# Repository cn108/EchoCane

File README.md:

# EchoCane — Arduino Nano Smart-Cane Prototype

**A safety-first embedded systems project: portable C++ policy core, Arduino Nano firmware, HC-SR04 sensing, PWM haptic drive, KiCad hardware and a documented verification trail.**

EchoCane is an experimental supplementary mobility aid that measures the distance
to the nearest surface with an HC-SR04 ultrasonic sensor and gives graded tactile
and audible warnings. This repository reconstructs the concept as a complete,
testable embedded-engineering portfolio project: portable C++ policy code,
Arduino Nano firmware, Wokwi simulation assets, native unit tests, a KiCad
carrier board, manufacturing outputs and engineering documentation.

> **Project intent:** this is an engineering case study, not a medical device or
a validated navigation product. The interesting part is the discipline around
it: bounded sensing, explicit fault behaviour, host-testable policy code,
power/thermal checks, editable PCB sources and an honest limitations register.

> **Safety notice**
> EchoCane is an experimental supplementary aid. It is **not** a replacement for
> a conventional mobility cane and has **not** been validated with users or on
> physical hardware. The distance thresholds in this repository are demonstration
> parameters, not safety limits. Do not use this design as a sole mobility aid.

> **Evidence notice**
> No physical Arduino, sensor, motor or PCB was available. Firmware compilation,
> host unit tests, schematic/PCB checks and an ngspice driver simulation were
> executed. Wokwi assets were validated structurally, but the Wokwi scenarios
> were **not executed** here because the Wokwi CLI and CI token were unavailable.
> Simulation is not physical validation.

## Contents

- [The problem](#the-problem)
- [What this project demonstrates](#what-this-project-demonstrates)
- [Demonstrated behaviour](#demonstrated-behaviour)
- [Status at a glance](#status-at-a-glance)
- [Visual gallery](#visual-gallery)
- [Features](#features)
- [Technology stack](#technology-stack)
- [Architecture](#architecture)
- [Repository layout](#repository-layout)
- [Quick start](#quick-start)
- [PCB](#pcb)
- [Engineering decisions and trade-offs](#engineering-decisions-and-trade-offs)
- [Pin map](#pin-map)
- [Audit corrections](#audit-corrections)
- [Engineering limitations](#engineering-limitations)
- [Documentation](#documentation)
- [License](#license)

## The problem

A white cane is effective because it gives direct, continuous mechanical feedback
about the ground and nearby objects. An electronic aid can complement it by
warning about obstacles before contact, but it introduces new failure modes:
sensor dropouts, blind angles, false confidence and output masking. EchoCane is
therefore designed around an explicit safety rule:

**A failed or unavailable sensor must never be reported as an obstacle-free path.**

The project explores that rule through a small, understandable system rather than
claiming to solve navigation for visually impaired users.

## What this project demonstrates

- **Safety-first firmware policy.** Invalid sensor readings never map to a
  clear-path result; the system moves through `CAUTION`/`FAULT`, requires
  consecutive confirmations, and only recovers after consecutive valid reads.
- **A testable embedded architecture.** Classification, hysteresis, debounce,
  scheduling and mode policy live in a portable C++ library with no Arduino
  dependency; hardware-specific `pulseIn`, `analogWrite`, `tone` and `millis`
  adapters stay at the edge.
- **Resource-aware AVR work.** The Nano build is constrained and measured:
  **10,766 / 30,720 bytes flash (35.0%)** and **777 / 2,048 bytes RAM (37.9%)**.
- **Real hardware engineering.** A complete KiCad 10 schematic and 2-layer PCB,
  editable sources, Gerbers, Excellon drill, drill map, STEP, schematic/PCB
  previews and an independent ERC/DRC/parity trail.
- **Analog and power reasoning.** The motor driver was sized around the loaded
  ATmega328P GPIO, R2 loading and a forced-beta target; the 1N4007 was checked
  against the actual 976.56 Hz PWM period and the design-current margins.
- **Reproducible evidence.** Deterministic schematic/PCB generators,
  cross-artifact validators, native unit tests and simulator assets are checked
  into the repository instead of being described only in prose.
- **Engineering honesty.** The audit findings, unresolved physical-validation
  gaps and design limitations are published alongside the passing checks.

### How to review this repository

| If you have… | Start here |
|---|---|
| 2 minutes | This README, then the [schematic](hardware/schematic/EchoCane-schematic.pdf) |
| 10 minutes | [Architecture](docs/architecture.md) and [circuit explanation](docs/circuit-explanation.md) |
| 30 minutes | [Independent audit](docs/audit-report.md), [requirements](docs/requirements.md) and [testing strategy](docs/testing-strategy.md) |
| A hardware/embedded interview | [Engineering decisions](#engineering-decisions-and-trade-offs), [pin map](#pin-map), [limitations](#engineering-limitations) |

## Demonstrated behaviour

| Measured distance | Alert level | Haptic pattern | Buzzer (Assist/Diagnostic) | LED |
|---|---|---|---|---|
| > 150 cm | `CLEAR` | off | off | short heartbeat |
| 80–150 cm inclusive | `CAUTION` | 40 %, 180 ms on / 320 ms off | 1800 Hz, 60 ms / 1140 ms | 120 ms blink |
| < 80 cm | `DANGER` | 100 %, 400 ms on / 120 ms off | 2400 Hz, 90 ms / 210 ms | solid |
| invalid / timeout | `CAUTION` first, then `FAULT` | fault pattern | 1000 Hz fault pattern | fast fault blink |

Hysteresis is asymmetric: a warning engages at the threshold but releases only
after the distance improves by 10 cm. This prevents chatter around 80 cm and
150 cm. The exact policy is in
[`ObstacleDetector.cpp`](firmware/lib/echocane_core/src/ObstacleDetector.cpp)
and is covered by unit tests.

A confirmed sensor fault requires **3 consecutive invalid acquisitions**. Recovery
requires **3 consecutive valid acquisitions**, and the system remains at least at
`CAUTION` while degraded or recovering. A failed acquisition holds the last
warning rather than clearing it.

## Status at a glance

| Check | Result | Evidence |
|---|---|---|
| Arduino Nano firmware build | **PASS** — 10,766 / 30,720 bytes flash (35.0 %), 777 / 2,048 bytes RAM (37.9 %) | PlatformIO `nanoatmega328` |
| Host unit tests | **PASS** — 25 / 25 | `pio test -e native` |
| Wokwi structural validation | **PASS** — 6 diagrams with explicit pin/stimulus mappings, 0 warnings | `python tests/validate_simulation.py` |
| Wokwi scenario execution | **NOT VERIFIED (NOT RUN)** — CLI/token unavailable | no serial logs claimed |
| Schematic ERC | **PASS** — 0 errors, 0 warnings | `hardware/verification/schematic-erc.rpt` |
| PCB DRC | **PASS** — 0 DRC violations, 0 unconnected pads, 0 schematic-parity issues | `hardware/verification/pcb-drc.rpt` |
| Cross-artifact consistency | **PASS** — 12 nets, 19 components, 15 BOM rows, 8 Wokwi links agree | `python tests/validate_hardware.py` |
| Driver design margins | **PASS** — 270 Ω, 4.2 V loaded GPIO, 11.0 mA base, forced beta 9.10 | `simulation/simulide/driver-analysis.json` |
| ngspice driver simulation | **EXECUTED** — 12.04 mA base, 104.37 mA motor, 0.0945 V Vce, 5.63 V flyback clamp | `simulation/simulide/ngspice-results.txt` |
| Independent engineering audit | **PASS** for every available check; physical/external checks remain open | [`docs/audit-report.md`](docs/audit-report.md) |
| Remote GitHub Actions execution | **PASS** — firmware/tests and KiCad ERC/DRC jobs completed successfully on GitHub | [EchoCane CI run 43788851832](https://github.com/cn108/EchoCane/actions/runs/43788851832) |
| Physical hardware / user validation | **NOT VERIFIED (not performed)** | no hardware available |

## Visual gallery

<p align="center">
  <em>A4 schematic with visible functional-block wiring; 3D top render of the 100 × 85 mm carrier PCB.</em>
</p>

Additional views: [schematic PDF](hardware/schematic/EchoCane-schematic.pdf),
[PCB PDF](hardware/pcb/EchoCane-pcb.pdf),
[3D bottom](images/EchoCane-3d-bottom.png),
[driver waveform](images/driver-waveform.svg).

## Features

- Cooperative application loop with 60 ms sensor scans, 5 ms button polling and
  scheduled haptic/audio/LED patterns. The HC-SR04 acquisition is bounded but
  blocking for up to 25 ms; it is not a hard-real-time loop.
- Five-sample median filter, asymmetric hysteresis, invalid-reading handling,
  timeout detection, fault confirmation and recovery.
- Three operating modes: **Assist** (haptic + audio), **Quiet** (haptic only) and
  **Diagnostic** (full warnings plus faster telemetry).
- Portable `echocane_core` library with no Arduino dependencies; host-testable
  policy and hardware adapters behind small interfaces.
- Serial diagnostics with a stable machine-readable `EC|...` telemetry record.
- Complete KiCad 10 schematic, 2-layer carrier PCB, 3D render, Gerbers and drill
  files.
- Reproducible hardware generators for the schematic, PCB and BOM.

## Technology stack

| Layer | Tool / part |
|---|---|
| Microcontroller | Arduino Nano, ATmega328P, classic 5 V, 16 MHz |
| Firmware | C++17, Arduino framework, PlatformIO |
| Host tests | PlatformIO native environment + Unity |
| Simulation | Wokwi (Arduino Nano, HC-SR04, LEDs, buzzer, button) |
| Supplementary circuit analysis | ngspice transient model; SimulIDE build guide |
| PCB | KiCad 10.0.8, `kicad-cli`, Docker |
| CI | GitHub Actions (build, tests, validators, KiCad checks, optional Wokwi) |

## Architecture

```mermaid
flowchart LR
  HC["HC-SR04<br/>D9 TRIG / D10 ECHO"] --> SM[SensorManager<br/>Arduino adapter]
  BTN["Mode button<br/>D2"] --> DB[ButtonDebouncer<br/>portable]
  SM -->|DistanceReading| EC[EchoCaneController<br/>portable policy]
  DB -->|validated press| EC
  EC --> HP[HapticController<br/>D6 PWM]
  EC --> AU[AudioController<br/>D8 tone]
  EC --> LD[LedIndicator<br/>D7]
  EC --> SR[SerialReporter<br/>115200 baud]
```

The core owns classification, hysteresis, fault/recovery, mode selection and
alert-pattern selection. The Arduino adapters own pins, `pulseIn`, `analogWrite`,
`tone` and `millis`. `EchoCaneController` can therefore be compiled and tested on
a host without an Arduino.

## Repository layout

```text
EchoCane/
├── firmware/
│   ├── include/                 # Arduino-facing adapters and pin map
│   ├── src/                     # SensorManager, outputs, main.cpp
│   ├── lib/echocane_core/       # portable policy library
│   └── test/test_core/          # 25 Unity tests, native environment
├── hardware/
│   ├── kicad/                   # schematic, PCB, project, netlist
│   ├── schematic/               # PDF and SVG
│   ├── pcb/                     # PDF, SVG, STEP
│   ├── gerber/                  # Gerbers, Excellon drill, drill map, job file
│   ├── bom/                     # design BOM
│   ├── verification/            # ERC/DRC reports and board statistics
│   └── generate_*.py            # reproducible generators
├── simulation/
│   ├── wokwi/                   # diagram.json, wokwi.toml, scenarios
│   ├── simulide/                # guide, ngspice model, driver calculations
│   └── scenarios/               # scenario matrix
├── tests/                       # structural, cross-artifact and Wokwi runners
├── docs/                        # engineering documentation
├── images/                      # rendered evidence
├── .github/workflows/           # CI and optional Wokwi job
├── platformio.ini
├── README.md
└── LICENSE
```

## Quick start

### Prerequisites

- Python 3.11+ and [PlatformIO](https://platformio.org/) (the repository uses a
  local `.venv` on Windows).
- VS Code with the PlatformIO and Wokwi extensions for interactive simulation.
- Docker for reproducing the native tests or KiCad checks on a machine without a
  host toolchain.
- KiCad 10 for opening the PCB project; `kicad-cli` for the command-line checks.

### Build and test without hardware or a Wokwi token

```bash
# from the repository root
python -m venv .venv
# Windows: .venv/Scripts/pip install platformio
# Linux/macOS: .venv/bin/pip install platformio
.venv/Scripts/pio run -e nanoatmega328
.venv/Scripts/pio test -e native

python tests/validate_simulation.py
python tests/validate_hardware.py
```

On Linux/macOS, use `.venv/bin/pio`. Native tests use the host compiler and do
not require an Arduino, a sensor or a Wokwi subscription.

Docker equivalents:

```bash
# native unit tests
MSYS_NO_PATHCONV=1 docker run --rm -v "$PWD:/work" -w /work \
  python:3.12-bookworm bash -lc \
  'python -m pip install -q platformio; pio test -e native'

# ERC and DRC (reports are written into the workspace)
docker run --rm -v "$PWD:/work" -w /work kicad/kicad:10.0 bash -lc '
  kicad-cli sch erc --severity-all --exit-code-violations \
    -o hardware/verification/schematic-erc.rpt \
    hardware/kicad/EchoCane.kicad_sch &&
  kicad-cli pcb drc --severity-all --exit-code-violations \
    --schematic-parity --refill-zones \
    -o hardware/verification/pcb-drc.rpt \
    hardware/kicad/EchoCane.kicad_pcb'
```

### Run the Wokwi simulation

1. Build the Nano firmware: `pio run -e nanoatmega328`.
2. Open **`simulation/wokwi`** as the VS Code workspace folder (or select
   `simulation/wokwi/wokwi.toml` as the Wokwi configuration). The TOML paths
   resolve to the repository root's `.pio` build.
3. Open `diagram.json` and start the Wokwi simulation. The main diagram starts
   with the HC-SR04 at 300 cm.
4. Drag the HC-SR04 distance control to 120 cm and then 50 cm. Confirm the serial
   telemetry changes to `level=CAUTION` and `level=DANGER`; the haptic LED and
   buzzer follow the configured patterns. The vibration motor is represented by
   a PWM-driven LED because Wokwi has no vibration-motor part.
5. Press the mode button to cycle `ASSIST → QUIET → DIAGNOSTIC`.
6. For sensor-fault behaviour, open
   `scenarios/diagrams/sensor_fault.json`; ECHO is tied to GND, so the firmware
   must report `DEGRADED` and then `FAULT`, never `free=1`.

The five automated scenarios and their per-scenario diagrams are listed in
[`simulation/scenarios/README.md`](simulation/scenarios/README.md). They require
the Wokwi CLI and `WOKWI_CLI_TOKEN`:

```bash
python tests/run_wokwi_scenarios.py --dry-run   # show commands, no token needed
export WOKWI_CLI_TOKEN=...                      # never commit this value
python tests/run_wokwi_scenarios.py
```

The local build, host tests, ERC and DRC do **not** require a token.

## PCB

The carrier board is **100 × 85 mm**, 2-layer, 1.6 mm FR-4, designed around the
classic 30-pin Arduino Nano module. It includes an HC-SR04 4-pin connector, a
2-pin vibration-motor connector, a PN2222A low-side switch with a 270 Ω base
resistor and 10 kΩ pull-down, a 1N4007 flyback diode, motor supply decoupling, a
mode button with an RC debounce capacitor, a status LED, a buzzer and four M3
mounting holes.

| Item | Result |
|---|---|
| Schematic | KiCad 10, A4 landscape, ERC 0 errors / 0 warnings |
| PCB | 15 electrical footprints + 4 mounting holes, all tracks routed |
| DRC | 0 violations, 0 unconnected pads, 0 schematic-parity issues |
| Board statistics | 63 PTH pads, 4 NPTH, 0 vias, 0.5 mm minimum track, 0.75 mm minimum drill |
| Manufacturing | Gerbers, Excellon drill, drill map PDF, Gerber job file, STEP |
| 3D | Top and bottom renders; the Nano module's vendor model is not in the installed KiCad library, so A1 is shown by its footprint outline (see the audit report) |

**Preview:** [schematic PDF](hardware/schematic/EchoCane-schematic.pdf) ·
[PCB PDF](hardware/pcb/EchoCane-pcb.pdf) ·
[Gerber directory](hardware/gerber/) ·
[3D bottom](images/EchoCane-3d-bottom.png)

The schematic is drawn on **A4 landscape** as labelled functional blocks with
visible local wiring; global labels are used only for the long
Nano-to-peripheral signal runs. It is an editable KiCad schematic, not only an
image or PDF.

The sole 5 V source is the Nano's USB connection. On a classic Nano, USB VBUS
passes through the module's onboard Schottky diode to the 5 V rail; the Nano 5V
pin is an **output**, and the carrier has no external 5 V input. Do not backfeed
the `+5V` net while USB is connected. The `PWR_FLAG` is on GND only because the
Nano's 5V pin already drives `+5V`; adding a second +5 V flag would conflict in
ERC.

### Power Design

**Power Design Disclaimer:** The v0.1 schematic is powered directly via the Arduino Nano's USB port for prototyping. The vibration motor's stall current may exceed the USB port's safe limits. The final production design will include a dedicated 5V voltage regulator and a Li-ion battery management circuit.

The 1N4007 flyback diode was checked against D6's **976.56 Hz** Timer0A PWM
(1.024 ms period). Its 1 A average / 30 A surge ratings are far above the 100 mA
design point, and its conservative 30 µs recovery interval is only about 2.9% of
the period. No diode change is justified at this frequency and current; the
1N4007 and PCB remain unchanged.

The board has not been fabricated, assembled or electrically tested. Gerbers are
design outputs, not manufacturing approval.

### Reproduce the hardware artifacts

```bash
# schematic, netlist, BOM, ERC
MSYS_NO_PATHCONV=1 docker run --rm -v "$PWD:/work" -w /work \
  kicad/kicad:10.0-full bash -lc '
  python3 hardware/generate_schematic.py &&
  kicad-cli sch erc --severity-all --exit-code-violations \
    -o hardware/verification/schematic-erc.rpt \
    hardware/kicad/EchoCane.kicad_sch &&
  kicad-cli sch export netlist --format kicadsexpr \
    -o hardware/kicad/EchoCane.net hardware/kicad/EchoCane.kicad_sch'

# PCB from the netlist, then DRC
MSYS_NO_PATHCONV=1 docker run --rm -v "$PWD:/work" -w /work \
  kicad/kicad:10.0-full bash -lc '
  python3 hardware/generate_pcb.py &&
  kicad-cli pcb drc --severity-all --exit-code-violations \
    --schematic-parity --refill-zones \
    -o hardware/verification/pcb-drc.rpt \
    hardware/kicad/EchoCane.kicad_pcb'
```

The detailed layer/export commands are in
[`docs/hardware-design.md`](docs/hardware-design.md).

## Engineering decisions and trade-offs

| Decision | Why it was chosen | What it costs |
|---|---|---|
| **270 Ω base resistor + PN2222A** | Uses the loaded-GPIO bound, includes R2 loading and meets the forced-beta-10 target at 100 mA | Motor current above the ~110 mA forced-beta-10 ceiling is not covered; stall current is unverified |
| **USB-only 5 V architecture** | The Nano's USB input is the intended source; no unvalidated charger or second regulator is added | The carrier is tethered; no external 5 V input or ORing/backfeed protection is fitted |
| **1N4007 flyback diode retained** | 1 A / 30 A / 1000 V ratings and ≤30 µs recovery are adequate at 976.56 Hz and 100 mA | It is not a fast-recovery/Schottky part; revisit if PWM frequency or stall current rises |
| **Portable `echocane_core` library** | Policy can be compiled and tested on the host without Arduino headers | Hardware adapters remain thin and must be reviewed separately |
| **Wokwi actuator proxy** | A PWM LED lets the command path be exercised without a vibration-motor model | It does not prove tactile output, motor torque or acoustic behaviour |
| **Local wires + long-distance labels** | Local block circuits are visually traceable; Nano-to-block nets stay readable | Cross-sheet connectivity is label-based, not one continuous drawn wire |
| **A4 landscape schematic** | Compact enough to read as a single engineering sheet while keeping the Nano central | More constrained placement than an A3 sheet; labels and sections must be kept disciplined |

## Pin map

| Signal | Nano pin | ATmega328P port | Connects to |
|---|---|---|---|
| HC-SR04 TRIG | D9 | PB1 | J1 pin 2 |
| HC-SR04 ECHO | D10 | PB2 | J1 pin 3 |
| Haptic PWM | D6 | PD6 / Timer0A | R1 → Q1 base |
| Buzzer | D8 | PB0 | R4 → BZ1 |
| Mode button | D2 | PD2 | SW1 to GND, active low |
| Status LED | D7 | PD7 | R3 → D2 |
| +5 V | 5V | — | J1.1, J2.1, D1 cathode, C1, C2 |
| GND | GND | — | J1.4, Q1 emitter, R2, C1, C2, C3, D2 cathode, SW1, BZ1 |

The same assignments are asserted across `Pins.h`, the KiCad netlist, the BOM
and the Wokwi diagram by `tests/validate_hardware.py`.

## Audit corrections

An independent audit rechecked the full repository rather than relying on the
initial status table. It corrected the forced-beta inequality in the driver
calculation, changed R1 from 1 kΩ to 330 Ω, then found that the 330 Ω result still
assumed an ideal 5 V GPIO and omitted the R2 loading. The final loaded-GPIO
calculation uses the ATmega328P datasheet VOH of 4.2 V at 20 mA, a 270 Ω resistor
and a 10 kΩ pull-down: 11.11 mA from the pin, 10.99 mA into the base and forced
beta 9.10 at the 100 mA design point. The 300 Ω case is also above the calculated
296.4 Ω limit and was rejected. The audit also removed an unrepresented optional
H5–H6 BOM row; moved C2 to give the two 5 mm capacitors mechanical clearance;
restored the board title-block revision; strengthened Wokwi validation to assert
exact GPIO/stimulus mappings; removed dead configuration; added an overflow-safe
echo conversion; and expanded the native suite from 18 to 25 tests. All generated
hardware outputs were regenerated. The full findings, evidence and remaining gaps
are in [`docs/audit-report.md`](docs/audit-report.md) and
[`docs/limitations-register.md`](docs/limitations-register.md).

## Engineering limitations

- **No physical validation.** No hardware was purchased or assembled. The
  firmware, PCB and simulation have not been tested against a real HC-SR04,
  vibration motor, buzzer or power supply.
- **Wokwi distance automation.** Wokwi's HC-SR04 does not expose a documented
  distance automation control. The automated scenarios therefore use static
  per-scenario diagrams and the moving-away case is a documented manual
  procedure. The scenarios were structurally validated but not executed here.
- **No vibration motor in Wokwi.** A PWM-driven LED and serial telemetry stand in
  for the actuator command. This proves the command path, not tactile output.
- **SimulIDE is not installed.** A validated `.simu` file is not included. The
  repository provides a precise SimulIDE build guide, executable design
  calculations and an executed ngspice transient model of the driver. The motor
  is a lumped 47 Ω / 10 mH model; it is not a tactile or acoustic validation.
- **Sensor physics.** Ultrasonic sensing is poor for soft, angled, narrow,
  transparent or cloth-like obstacles, and cannot detect drop-offs, stairs or
  overhead objects. See [`docs/safety-analysis.md`](docs/safety-analysis.md).
- **Demonstration thresholds.** 150 cm and 80 cm are configurable engineering
  defaults. They are not clinically or ergonomically validated.
- **PCB is unmanufactured.** DRC/ERC clean results do not prove assembly yield,
  EMC, thermal behaviour or connector reliability. The Nano module's 3D model is
  absent from the installed KiCad library, so it is not in the STEP/render. A
  CC0 candidate model exists, but it was not independently dimensionally verified
  and is therefore not included; see [`docs/limitations-register.md`](docs/limitations-register.md).
- **Power.** The design assumes a commercially manufactured regulated 5 V USB
  source. No lithium-ion charging circuit is designed or validated. The design
  budget is 174.7 mA for a 100 mA motor, 25 mA Nano allowance, 15 mA sensor peak,
  11.1 mA base drive, 10 mA buzzer and 13.6 mA LED, leaving 325.3 mA of nominal
  USB headroom. Motor stall current is unknown and can exceed the 100 mA design
  point; the selected drive supports only about 109.9 mA at forced beta 10, so a
  larger motor requires a new driver/current check.

## Documentation

- [Requirements](docs/requirements.md)
- [Architecture](docs/architecture.md)
- [Hardware design](docs/hardware-design.md)
- [Circuit explanation and calculations](docs/circuit-explanation.md)
- [Software design](docs/software-design.md)
- [Independent engineering audit](docs/audit-report.md)
- [Outstanding limitations register](docs/limitations-register.md)
- [Testing strategy and results](docs/testing-strategy.md)
- [Simulation limitations](docs/simulation-limitations.md)
- [Safety analysis](docs/safety-analysis.md)
- [Development history and milestones](docs/development-history.md)
- [Scenario matrix](simulation/scenarios/README.md)

## Author

Built and documented as an embedded-systems portfolio project by
**[@cn108](https://github.com/cn108)**.

## License

MIT — see [LICENSE](LICENSE). The design is provided as an educational portfolio
artifact without warranty or fitness for a particular purpose.

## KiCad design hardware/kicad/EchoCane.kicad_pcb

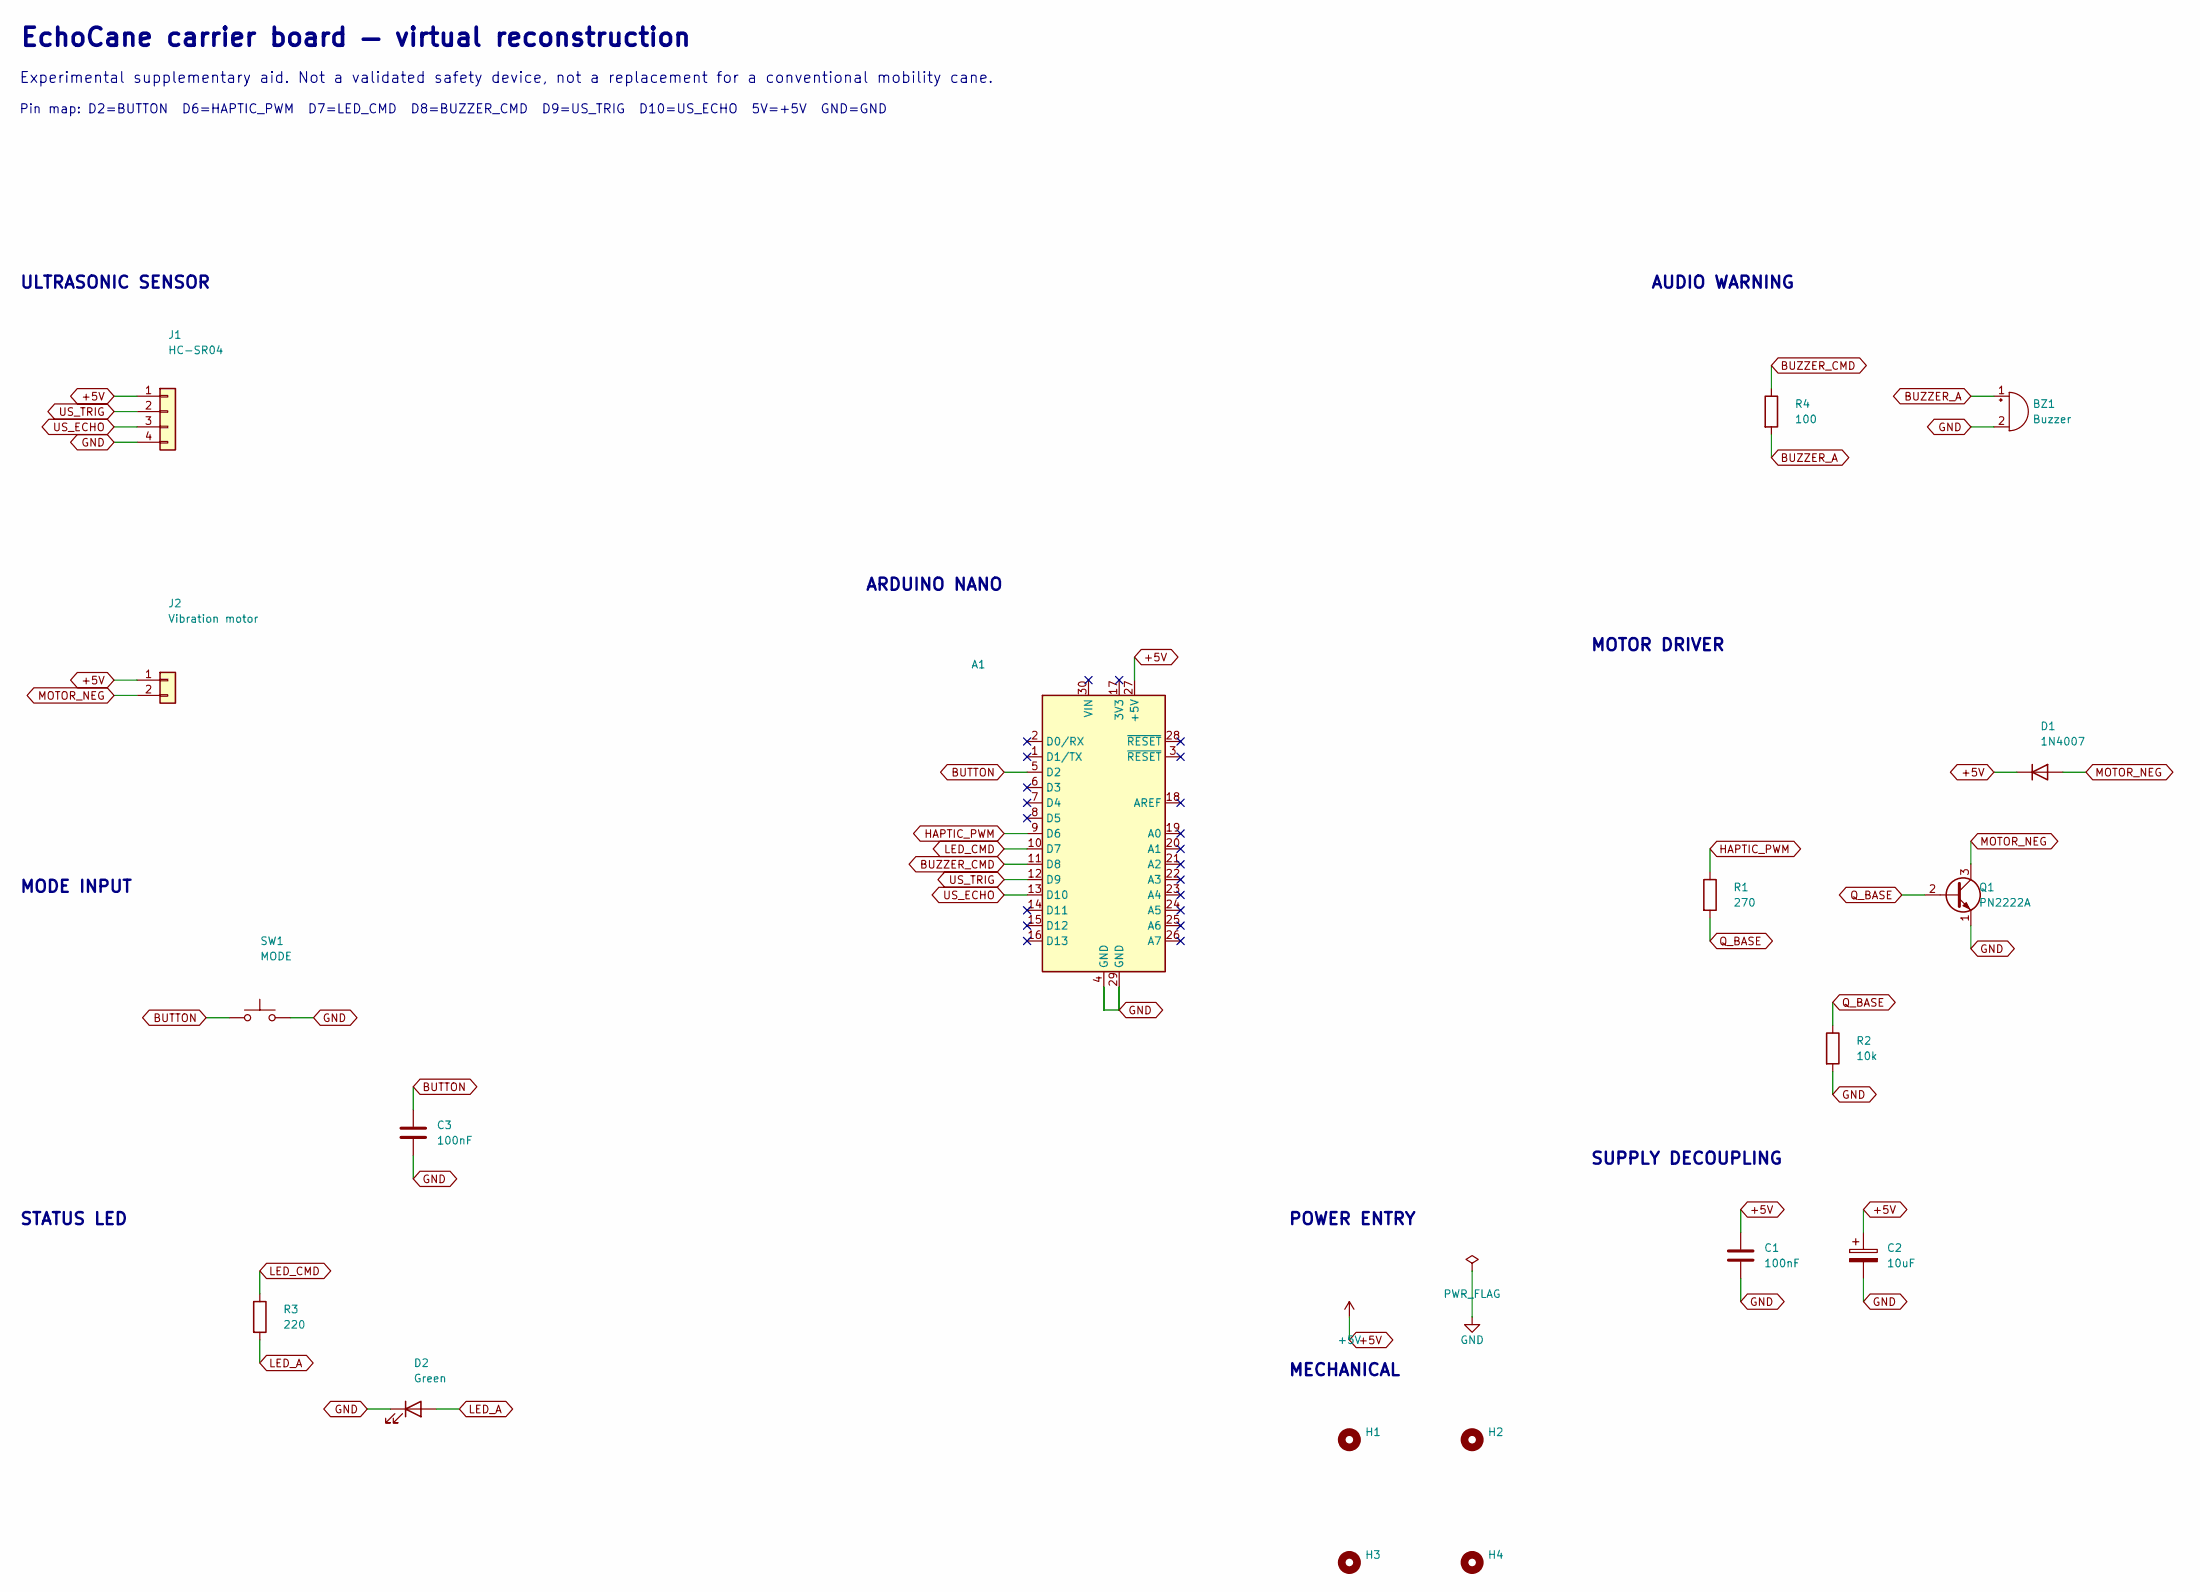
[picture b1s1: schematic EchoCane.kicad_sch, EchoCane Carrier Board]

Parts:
A1: Arduino Nano v3.x; Arduino_Nano
BZ1: Buzzer; Buzzer_12x9.5RM7.6
C1, C3: 100nF; C_Disc_D5.0mm_W2.5mm_P5.00mm
C2: 10uF; CP_Radial_D5.0mm_P2.00mm
D1: 1N4007; D_DO-41_SOD81_P7.62mm_Horizontal
D2: Green; LED_D5.0mm
H1, H2, H3, H4: MountingHole; MountingHole_3.2mm_M3
J1: HC-SR04; PinHeader_1x04_P2.54mm_Vertical
J2: Vibration motor; PinHeader_1x02_P2.54mm_Vertical
Q1: PN2222A; TO-92_Inline
R1: 270; R_Axial_DIN0207_L6.3mm_D2.5mm_P7.62mm_Horizontal
R2: 10k; R_Axial_DIN0207_L6.3mm_D2.5mm_P7.62mm_Horizontal
R3: 220; R_Axial_DIN0207_L6.3mm_D2.5mm_P7.62mm_Horizontal
R4: 100; R_Axial_DIN0207_L6.3mm_D2.5mm_P7.62mm_Horizontal
SW1: MODE; SW_PUSH_6mm

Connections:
+5V: A1.27 (+5V), C1.1, C2.1, D1.1 (K), J1.1, J2.1
BUTTON: A1.5 (D2), C3.1, SW1.1
BUZZER_A: BZ1.1 (+), R4.2
BUZZER_CMD: A1.11 (D8), R4.1
GND: A1.4 (GND), A1.29 (GND), BZ1.2 (-), C1.2, C2.2, C3.2, D2.1 (K), J1.4, Q1.1 (E), R2.2, SW1.2
HAPTIC_PWM: A1.9 (D6), R1.1
LED_A: D2.2 (A), R3.2
LED_CMD: A1.10 (D7), R3.1
MOTOR_NEG: D1.2 (A), J2.2, Q1.3 (C)
Q_BASE: Q1.2 (B), R1.2, R2.1
US_ECHO: A1.13 (D10), J1.3
US_TRIG: A1.12 (D9), J1.2

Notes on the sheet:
EchoCane carrier board — virtual reconstruction
Experimental supplementary aid. Not a validated safety device, not a replacement for a conventional mobility cane.
Pin map: D2=BUTTON D6=HAPTIC_PWM D7=LED_CMD D8=BUZZER_CMD D9=US_TRIG D10=US_ECHO 5V=+5V GND=GND
ULTRASONIC SENSOR
MODE INPUT
STATUS LED
MOTOR DRIVER
AUDIO WARNING
SUPPLY DECOUPLING
ARDUINO NANO
POWER ENTRY
MECHANICAL

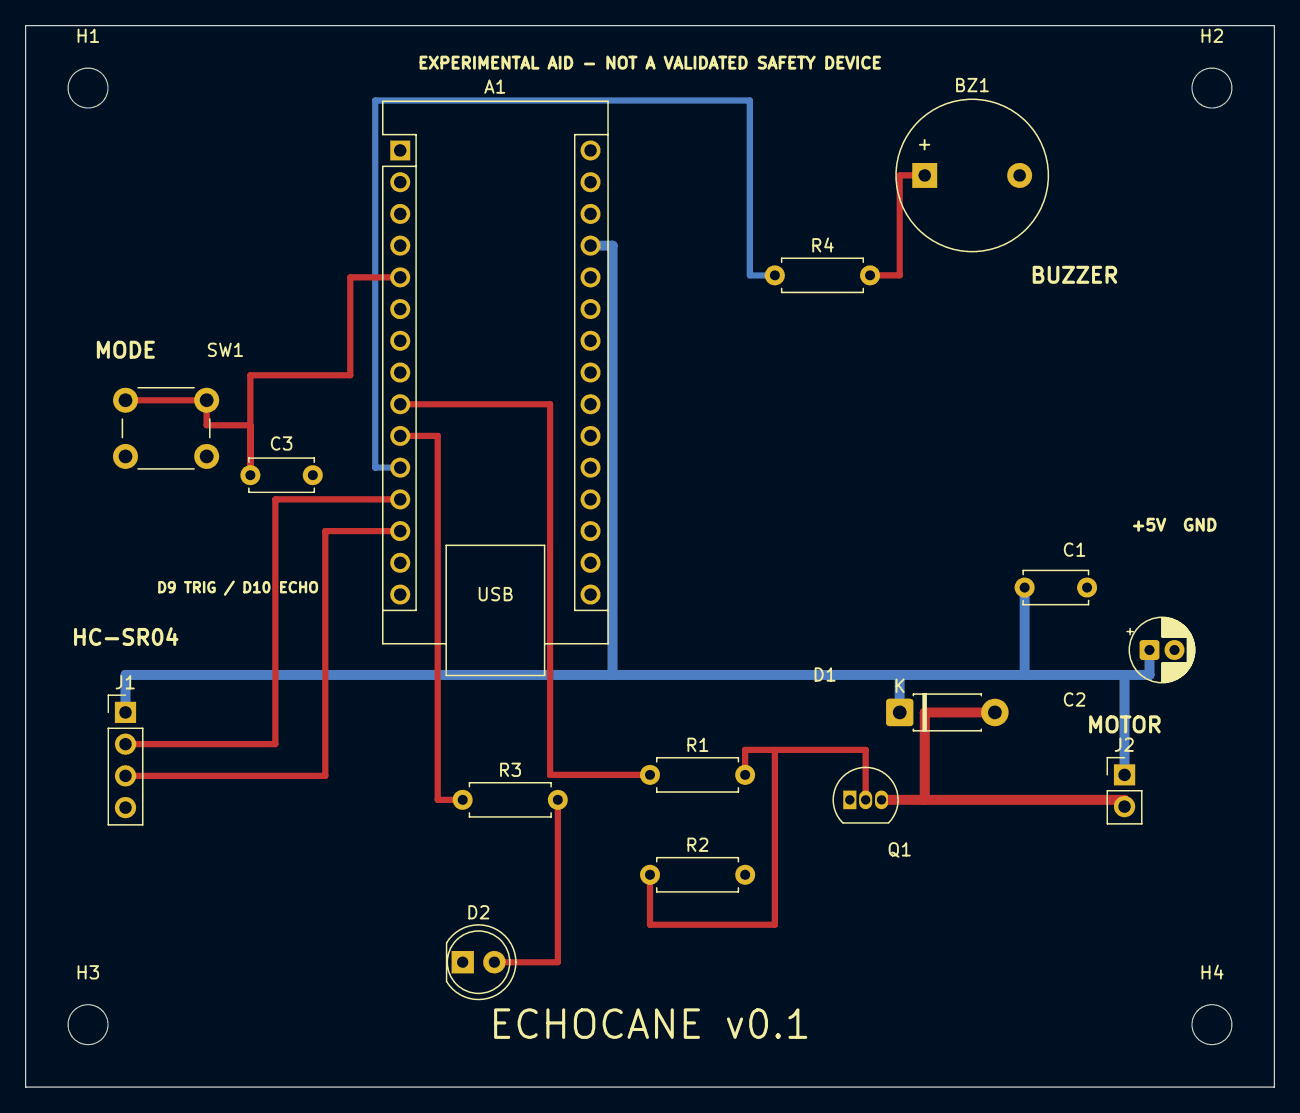
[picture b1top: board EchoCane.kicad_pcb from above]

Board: 2 copper layers, 100.0 x 85.0 mm, 19 parts (0 on the bottom side), 12 nets.

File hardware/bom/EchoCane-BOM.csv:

Reference,Value,Footprint,Description,Qty
A1,Arduino Nano v3.x,Module:Arduino_Nano,ATmega328P 5 V Arduino Nano module,1
J1,HC-SR04,Connector_PinHeader_2.54mm:PinHeader_1x04_P2.54mm_Vertical,4-pin HC-SR04 ultrasonic sensor connector,1
J2,Vibration motor,Connector_PinHeader_2.54mm:PinHeader_1x02_P2.54mm_Vertical,2-pin vibration motor connector,1
Q1,PN2222A,Package_TO_SOT_THT:TO-92_Inline,"NPN low-side motor switch, TO-92",1
R1,270,Resistor_THT:R_Axial_DIN0207_L6.3mm_D2.5mm_P7.62mm_Horizontal,Base current limit resistor,1
R2,10k,Resistor_THT:R_Axial_DIN0207_L6.3mm_D2.5mm_P7.62mm_Horizontal,Base pull-down resistor,1
D1,1N4007,Diode_THT:D_DO-41_SOD81_P7.62mm_Horizontal,Flyback diode across the motor,1
C1,100nF,Capacitor_THT:C_Disc_D5.0mm_W2.5mm_P5.00mm,"Motor supply decoupling, ceramic",1
C2,10uF,Capacitor_THT:CP_Radial_D5.0mm_P2.00mm,Motor supply bulk capacitor,1
SW1,MODE,Button_Switch_THT:SW_PUSH_6mm,"Mode push button, active low",1
C3,100nF,Capacitor_THT:C_Disc_D5.0mm_W2.5mm_P5.00mm,Button hardware debounce capacitor,1
R3,220,Resistor_THT:R_Axial_DIN0207_L6.3mm_D2.5mm_P7.62mm_Horizontal,Status LED series resistor,1
D2,Green,LED_THT:LED_D5.0mm,"Status indicator LED, 5 mm",1
R4,100,Resistor_THT:R_Axial_DIN0207_L6.3mm_D2.5mm_P7.62mm_Horizontal,Buzzer series resistor,1
BZ1,Buzzer,Buzzer_Beeper:Buzzer_12x9.5RM7.6,5 V piezo buzzer,1

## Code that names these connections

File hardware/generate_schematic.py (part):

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    add_path([j1_1, (snap(j1_1[0] - 7.62), j1_1[1]), (snap(j1_1[0] - 7.62), snap(j1_1[1] - 5.08))], "J1:1")
    body.append(power_symbol("power:+5V", snap(j1_1[0] - 7.62), snap(j1_1[1] - 5.08), "J1:1:symbol"))
    body.append(wire(*j1_2, snap(j1_2[0] - 5.08), j1_2[1], "J1:2:stub"))
    add_label("US_TRIG", snap(j1_2[0] - 5.08), j1_2[1], "J1:2", -1.0)
    body.append(wire(*j1_3, snap(j1_3[0] - 5.08), j1_3[1], "J1:3:stub"))
    add_label("US_ECHO", snap(j1_3[0] - 5.08), j1_3[1], "J1:3", -1.0)
    add_path([j1_4, (snap(j1_4[0] - 7.62), j1_4[1]), (snap(j1_4[0] - 7.62), snap(j1_4[1] + 5.08))], "J1:4")
    body.append(power_symbol("power:GND", snap(j1_4[0] - 7.62), snap(j1_4[1] + 5.08), "J1:4:symbol"))

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    d2_1 = pin("D2", "1")
    d2_2 = pin("D2", "2")
    body.append(wire(r3_1[0], r3_1[1], r3_1[0], snap(r3_1[1] - 5.08), "R3:1:stub"))
    add_label("LED_CMD", r3_1[0], snap(r3_1[1] - 5.08), "R3:1", 1.0)
    add_path([r3_2, (snap(r3_2[0] - 15.24), r3_2[1]), (snap(r3_2[0] - 15.24), d2_2[1])], "R3:2")
    body.append(wire(snap(r3_2[0] - 15.24), r3_2[1], snap(r3_2[0] - 15.24), snap(r3_2[1] + 5.08), "R3:2:label"))
    add_junction(snap(r3_2[0] - 15.24), r3_2[1], "LED_A")
    add_label("LED_A", snap(r3_2[0] - 15.24), snap(r3_2[1] + 5.08), "R3:2", -1.0)
    body.append(wire(snap(r3_2[0] - 15.24), d2_2[1], d2_2[0], d2_2[1], "R3:2:led"))
    body.append(wire(d2_1[0], d2_1[1], snap(d2_1[0] - 5.08), d2_1[1], "D2:1:gnd"))
    body.append(power_symbol("power:GND", snap(d2_1[0] - 5.08), d2_1[1], "D2:1:gnd:symbol"))
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    d1_1 = pin("D1", "1")
    d1_2 = pin("D1", "2")

    add_label("HAPTIC_PWM", *r1_1, "R1:1", -1.0)
    add_path([r1_2, (r1_2[0], q_b[1]), q_b], "R1:2:base")
    body.append(wire(r2_1[0], q_b[1], r2_1[0], r2_1[1], "R2:1:base"))
    add_junction(r2_1[0], q_b[1], "Q_BASE")
    add_label("Q_BASE", r1_2[0], q_b[1], "Q_BASE", -1.0)

    body.append(wire(r2_2[0], r2_2[1], r2_2[0], snap(r2_2[1] + 5.08), "R2:2:gnd"))
    body.append(power_symbol("power:GND", r2_2[0], snap(r2_2[1] + 5.08), "R2:2:gnd:symbol"))
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
    add_power("power:+5V", *j2_1, -5.08, 0, "J2:1")
    add_path([j2_2, (snap(j2_2[0] - 10.16), j2_2[1]), (snap(j2_2[0] - 10.16), q_c[1]), q_c], "J2:2:motor")
    add_label("MOTOR_NEG", snap(j2_2[0] - 10.16), j2_2[1], "J2:2", -1.0)
    body.append(wire(d1_2[0], d1_2[1], snap(j2_2[0] - 10.16), d1_2[1], "D1:2:motor"))
    add_junction(snap(j2_2[0] - 10.16), d1_2[1], "MOTOR_NEG")
    add_power("power:+5V", *d1_1, -5.08, 0, "D1:1")
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    r4_2 = pin("R4", "2")
    bz1_1 = pin("BZ1", "1")
    bz1_2 = pin("BZ1", "2")
    add_label("BUZZER_CMD", *r4_1, "R4:1", -1.0)
    add_path([r4_2, (snap(r4_2[0] + 20.32), r4_2[1]), (snap(r4_2[0] + 20.32), bz1_1[1])], "R4:2")
    body.append(wire(snap(r4_2[0] + 20.32), r4_2[1], snap(r4_2[0] + 20.32), snap(r4_2[1] + 5.08), "R4:2:label"))
    add_junction(snap(r4_2[0] + 20.32), r4_2[1], "BUZZER_A")
    add_label("BUZZER_A", snap(r4_2[0] + 20.32), snap(r4_2[1] + 5.08), "R4:2", -1.0)
    body.append(wire(snap(r4_2[0] + 20.32), bz1_1[1], bz1_1[0], bz1_1[1], "R4:2:buzzer"))
    body.append(wire(bz1_2[0], bz1_2[1], snap(bz1_2[0] - 12.7), bz1_2[1], "BZ1:2:gnd"))
    body.append(wire(snap(bz1_2[0] - 12.7), bz1_2[1], snap(bz1_2[0] - 12.7), snap(bz1_2[1] + 7.62), "BZ1:2:gnd:drop"))
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\t\t)
\t\t(uuid "e7c4e1a3-21a1-4df2-9f3e-2a1d8f4a1c12")
\t)
\t(text "Pin map: D2=BUTTON  D6=HAPTIC_PWM  D7=LED_CMD  D8=BUZZER_CMD  D9=US_TRIG  D10=US_ECHO  5V=+5V  GND=GND"
\t\t(at 30 31 0)
\t\t(effects
\t\t\t(font
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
